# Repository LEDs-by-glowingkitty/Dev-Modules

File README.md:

# Dev-Modules
A collection of development modules for electrical engineers, who work on new PCB designs.

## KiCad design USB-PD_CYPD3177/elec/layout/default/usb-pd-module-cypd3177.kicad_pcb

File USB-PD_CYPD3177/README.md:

# Dev-Module / USB-PD Module / CYPD3177
A PCB module for hardware developers who want to easily test and build prototypes that include the CYPD3177 USB-PD IC.

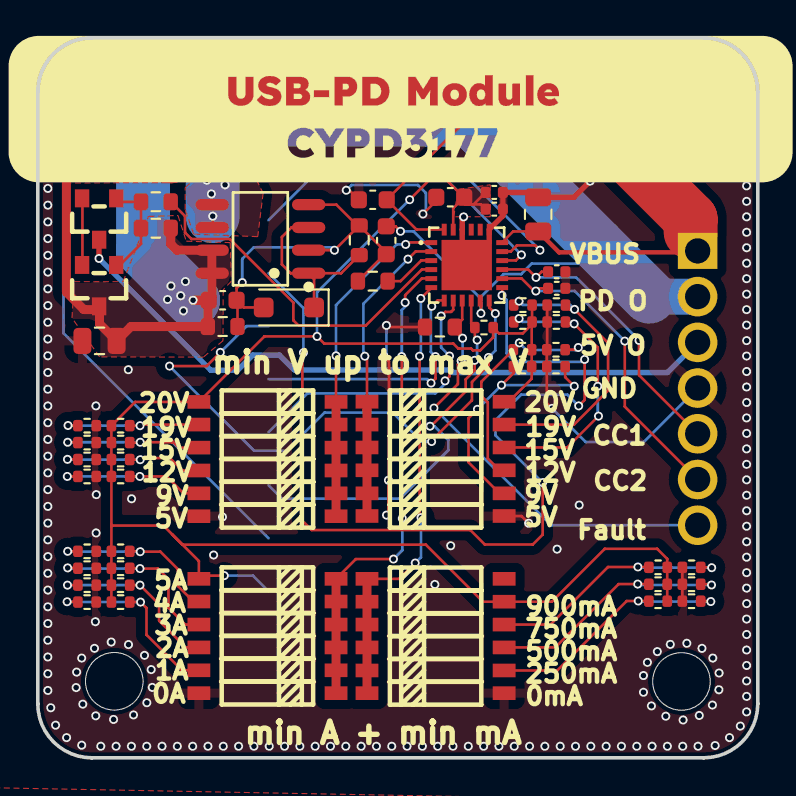
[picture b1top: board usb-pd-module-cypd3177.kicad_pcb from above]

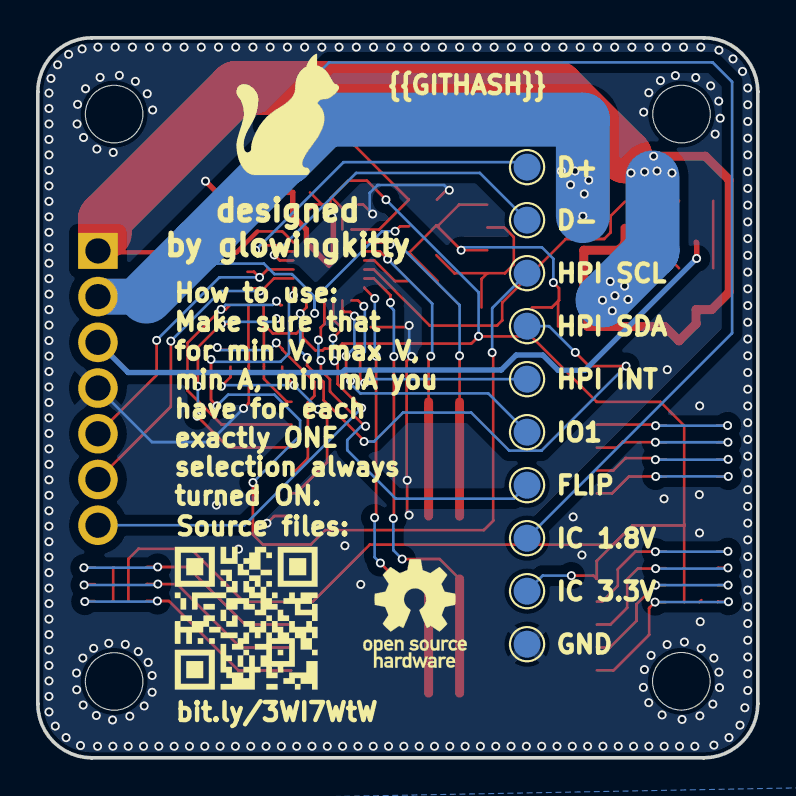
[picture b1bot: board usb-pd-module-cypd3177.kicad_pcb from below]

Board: 2 copper layers, 40.0 x 40.0 mm, 71 parts (10 on the bottom side), 41 nets.

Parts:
C1, C6: 16V 3.3uF X7R ±10% 0805 Multilayer Ceramic Capaci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; C0805
C2, C3, C7, C8: 50V 1uF X5R ±10% 0603 Multilayer Ceramic Capacito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; C0603
C4, C5: 50V 390pF NP0 ±5% 0402 Multilayer Ceramic Capacit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; C0402
C9, C10: 16V 100nF X7R ±10% 0402 Multilayer Ceramic Capaci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; C0402
DZ1: D_SOD-123F
Q1: SOP-8_L4.9-W3.9-P1.27-LS6.0-BL
Q2, Q3: SOT-23_L2.9-W1.3-P1.90-LS2.4-BR
R1: 100mW Thick Film Resistors 75V ±100ppm/℃ ±1% 10kΩ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; R0603
R2, R5: 100mW Thick Film Resistors 75V ±100ppm/℃ ±1% 1kΩ 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; R0603
R3, R4: 100mW Thick Film Resistors 75V ±100ppm/℃ ±1% 49.9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; R0603
R6: 100mW Thick Film Resistors 75V ±100ppm/℃ ±1% 100k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; R0603
R7: 62.5mW Thick Film Resistors 50V ±100ppm/℃ ±1% 2kΩ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; R0402
R8, R10, R12, R13, R14, R16, R18, R20, R21, R22, R24, R26, R28, R29, R30, R32, R34, R36, R37: 62.5mW Thick Film Resistors 50V ±100ppm/℃ ±1% 5.1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; R0402
R9, R17, R25, R33: 62.5mW Thick Film Resistors 50V ±100ppm/℃ ±1% 1kΩ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; R0402
R11, R19, R27, R35: 62.5mW Thick Film Resistors 50V ±100ppm/℃ ±1% 2.4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; R0402
R15, R23, R31: 62.5mW Thick Film Resistors 50V ±100ppm/℃ ±1% 10k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; R0402
U1, U2, U3, U4: SW-SMD_12P-L9.2-W5.4-P1.27-LS8.5
U5: CONN-TH_XY308-2.54-7P
U6, U7, U8, U9, U10, U11, U12, U13, U14, U15: TestPoint_Pad_D1.5mm
U16, U17, U18, U19: MountingHole_3.2mm_M3
U20: TQFN-24_L4.0-W4.0-P0.50-TL-EP2.8

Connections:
cc1: C4.1, U5.5, U20.15
cc2: C5.1, U5.6, U20.14
dminus: U8.1, U20.16
dplus: U7.1, U20.17
fault: R6.1, U5.7, U20.9
flip: R7.1, U15.1, U20.10
gate: Q2.1, Q3.1, R4.2, R5.1
gnd: C1.2, C4.2, C5.2, C6.2, C7.2, C8.2, C9.2, C10.2, R6.2, R9.2, R11.2, R13.2, R15.2, R17.2, R19.2, R21.2, R23.2, R25.2, R27.2, R29.2, R31.2, R33.2, R35.2, R37.2, U1.12, U2.7, U3.12, U4.7, U5.4, U6.1, U20.19, U20.22, U20.25
gpio_1: U14.1, U20.8
hpi_int: U13.1, U20.7
hpi_scl: U12.1, U20.13
hpi_sda: U11.1, U20.12
isnk_coarse: U3.1, U3.2, U3.3, U3.4, U3.5, U3.6, U20.5
isnk_fine: U4.1, U4.2, U4.3, U4.4, U4.5, U4.6, U20.6
power_out_5v_load_switch.p_mosfet_1-source: Q2.2, Q3.2
power_out_vbus_load_switch.dual_p_mosfet-gnd: C2.2, C3.2, DZ1.2, Q1.2, Q1.4, R1.2, R2.2, R3.2
power_out_vbus_load_switch.dual_p_mosfet-source: DZ1.1, Q1.1, Q1.3, R3.1
safe_pwr_en: R5.2, U20.4
vbus_fet_en: R2.1, U20.3
vbus_in: C1.1, C2.1, C6.1, Q1.7, Q1.8, Q2.3, R1.1, R4.1, U5.1, U20.18
vbus_max: U2.1, U2.2, U2.3, U2.4, U2.5, U2.6, U20.2
vbus_min: U1.1, U1.2, U1.3, U1.4, U1.5, U1.6, U20.1
vcc: Q3.3, U5.3
vccd: C7.1, U10.1, U20.24
vdc_out: C3.1, Q1.5, Q1.6, U5.2, U20.11
vddd: C8.1, C9.1, C10.1, R7.2, R8.1, R10.1, R12.1, R14.1, R16.1, R18.1, R20.1, R22.1, R24.1, R26.1, R28.1, R30.1, R32.1, R34.1, R36.1, U1.7, U2.12, U3.7, U4.11, U9.1, U20.23
voltage_dividers_and_dip_switches.coarse_current_min_1a_voltage_divider-out: R24.2, R25.1, U3.11
voltage_dividers_and_dip_switches.coarse_current_min_2a_voltage_divider-out: R26.2, R27.1, U3.10
voltage_dividers_and_dip_switches.coarse_current_min_3a_voltage_divider-out: R28.2, R29.1, U3.9
voltage_dividers_and_dip_switches.coarse_current_min_4a_voltage_divider-out: R30.2, R31.1, U3.8
voltage_dividers_and_dip_switches.fine_current_min_250ma_voltage_divider-out: R32.2, R33.1, U4.8
voltage_dividers_and_dip_switches.fine_current_min_500ma_voltage_divider-out: R34.2, R35.1, U4.9
voltage_dividers_and_dip_switches.fine_current_min_750ma_voltage_divider-out: R36.2, R37.1, U4.10
voltage_dividers_and_dip_switches.maximum_voltage_9v_voltage_divider-out: R16.2, R17.1, U2.8
voltage_dividers_and_dip_switches.maximum_voltage_12v_voltage_divider-out: R18.2, R19.1, U2.9
voltage_dividers_and_dip_switches.maximum_voltage_15v_voltage_divider-out: R20.2, R21.1, U2.10
voltage_dividers_and_dip_switches.maximum_voltage_19v_voltage_divider-out: R22.2, R23.1, U2.11
voltage_dividers_and_dip_switches.minimum_voltage_9v_voltage_divider-out: R8.2, R9.1, U1.11
voltage_dividers_and_dip_switches.minimum_voltage_12v_voltage_divider-out: R10.2, R11.1, U1.10
voltage_dividers_and_dip_switches.minimum_voltage_15v_voltage_divider-out: R12.2, R13.1, U1.9
voltage_dividers_and_dip_switches.minimum_voltage_19v_voltage_divider-out: R14.2, R15.1, U1.8

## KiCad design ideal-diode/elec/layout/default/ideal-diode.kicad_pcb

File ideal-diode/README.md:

# ideal-diode

Wooohooo a new package!

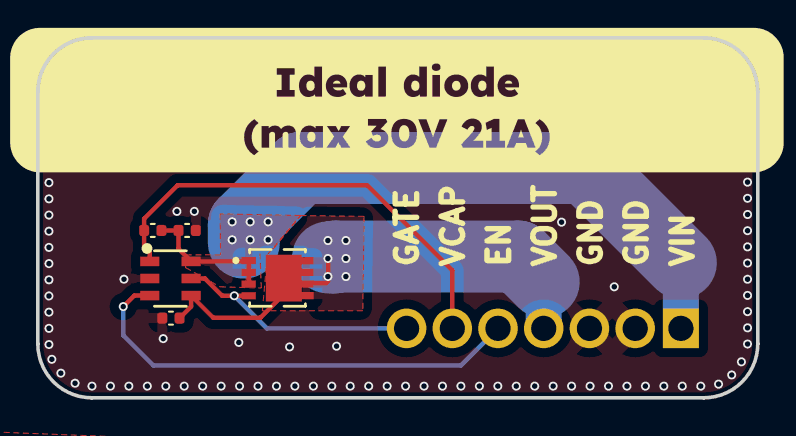
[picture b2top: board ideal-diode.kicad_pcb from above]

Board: 2 copper layers, 40.0 x 20.0 mm, 8 parts (0 on the bottom side), 6 nets.

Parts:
C1: 50V 22nF X7R ±10% 0402 Multilayer Ceramic Capacit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; C0402
C2, C3: 16V 100nF X7R ±10% 0402 Multilayer Ceramic Capaci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; C0402
Q1: PDFN-8_L3.2-W3.0-P0.65-LS3.3-BL-1
U1: SOT-23-6_L2.9-W1.6-P0.95-LS2.8-BL
U2: CONN-TH_XY308-2.54-7P
U3, U4: MountingHole_3.2mm_M3

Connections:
anode: C1.1, C2.1, Q1.1, Q1.2, Q1.3, U1.6, U2.1
cathode: C3.1, Q1.5, Q1.6, Q1.7, Q1.8, Q1.9, U1.4, U2.4
en: U1.3, U2.5
gate: Q1.4, U1.5, U2.7
gnd: C1.2, C3.2, U1.2, U2.2, U2.3
vcap: C2.2, U1.1, U2.6

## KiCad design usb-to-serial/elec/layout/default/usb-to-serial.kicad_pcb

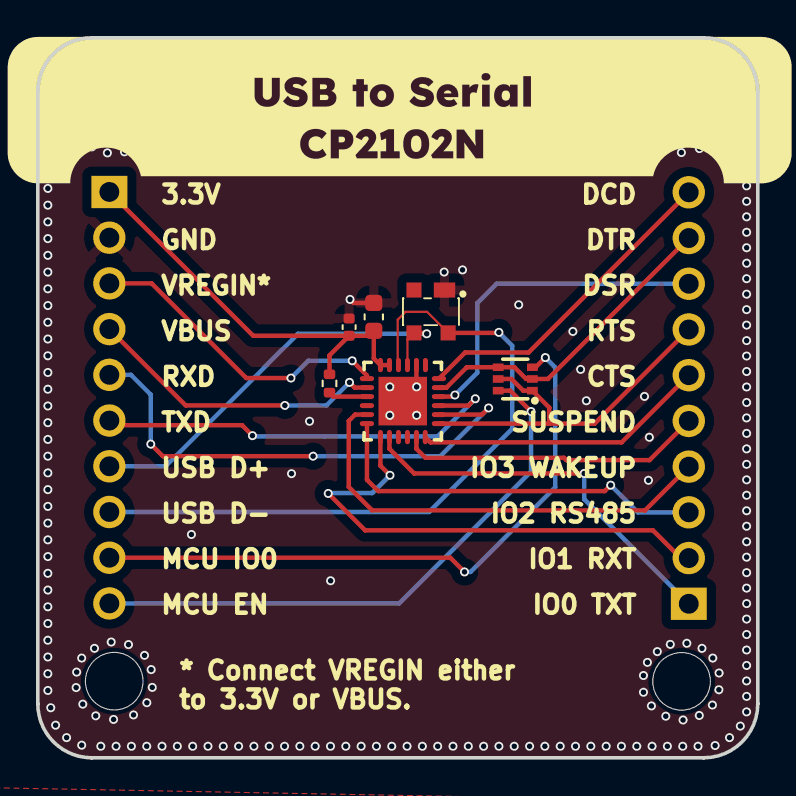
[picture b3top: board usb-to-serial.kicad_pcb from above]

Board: 2 copper layers, 40.0 x 40.0 mm, 12 parts (0 on the bottom side), 21 nets.

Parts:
C1: 16V 100nF X7R ±10% 0402 Multilayer Ceramic Capaci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; C0402
C2: 10V 10uF X5R ±10% 0603 Multilayer Ceramic Capacit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; C0603
R1: 62.5mW Thick Film Resistors 50V ±100ppm/℃ ±1% 1kΩ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; R0402
U1: SOT-143-4_L2.9-W1.3-P1.92-LS2.4-BL
U2: SC-70-6_L2.2-W1.3-P0.65-LS2.1-BR
U3: QFN-24_L4.0-W4.0-P0.50-TL-EP2.6
U4, U5: CONN-TH_10P-P2.54_MX128-2.54-10P-GN01-CU-Y-A
U6, U7, U8, U9: MountingHole_3.2mm_M3

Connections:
cts: U3.18, U5.6
dcd: U3.24, U5.10
dminus: U1.4, U3.4, U4.8
dplus: U1.3, U3.3, U4.7
dsr: U3.22, U5.8
dtr: U2.2, U2.4, U3.23, U5.9
gnd: C1.2, C2.2, U1.1, U3.2, U3.25, U4.2
gpio_0_txt: U3.14, U5.1
gpio_1_rxt: U3.13, U5.2
gpio_2_rs485: U3.12, U5.3
gpio_3_wakeup: U3.11, U5.4
mcu_en: U2.6, U4.10
mcu_io0: U2.3, U4.9
rstb: R1.1, U3.9
rts: U2.1, U2.5, U3.19, U5.7
rxd: U3.20, U4.5
suspend: U3.17, U5.5
txd: U3.21, U4.6
vbus: U3.8, U4.4
vio: C1.1, C2.1, R1.2, U3.5, U3.6, U4.1
vregin: U3.7, U4.3

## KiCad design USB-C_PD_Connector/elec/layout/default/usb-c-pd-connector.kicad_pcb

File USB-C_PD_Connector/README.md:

# Dev-Module / USB-C PD Connector
A PCB module for hardware developers who want to easily test and build prototypes that include a USB PD capable USB-C port (that can handle up to 100W at 20V 5A).

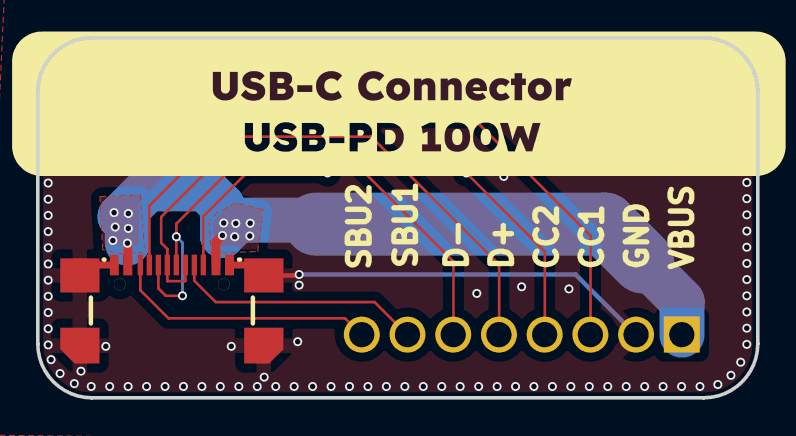
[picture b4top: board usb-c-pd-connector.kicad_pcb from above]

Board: 2 copper layers, 40.0 x 20.0 mm, 4 parts (0 on the bottom side), 8 nets.

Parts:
U1: USB-C-SMD_TYPE-C-31-M-22
U2: CONN-TH_XY308-2.54-8P
U3, U4: MountingHole_3.2mm_M3

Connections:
cc1: U1.4, U2.3
cc2: U1.10, U2.4
dm: U1.5, U1.7, U2.6
dp: U1.6, U1.8, U2.5
gnd: U1.1, U1.12, U1.13, U1.14, U1.15, U1.16, U2.2
sbu1: U1.9, U2.7
sbu2: U1.3, U2.8
vbus: U1.2, U1.11, U2.1

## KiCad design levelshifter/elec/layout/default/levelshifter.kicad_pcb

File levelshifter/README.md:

# levelshifter

Wooohooo a new package!

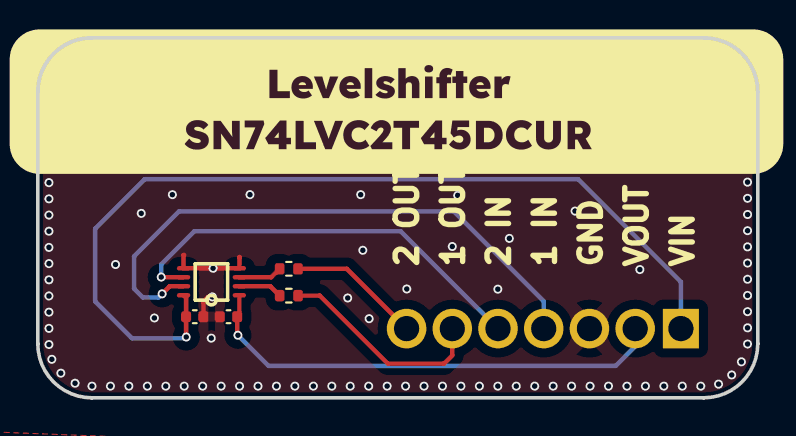
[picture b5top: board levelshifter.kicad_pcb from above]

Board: 2 copper layers, 40.0 x 20.0 mm, 8 parts (0 on the bottom side), 9 nets.

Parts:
C1, C2: 16V 100nF X7R ±10% 0402 Multilayer Ceramic Capaci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; C0402
R1, R2: 62.5mW Thick Film Resistors ±100ppm/℃ ±1% 62Ω 040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; R0402
U1: VSSOP-8_L2.4-W2.1-P0.50-LS3.2-BR
U2: CONN-TH_XY308-2.54-7P
U3, U4: MountingHole_3.2mm_M3

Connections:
a1: R1.2, U1.2
a2: R2.2, U1.3
b1: U1.7, U2.4
b2: U1.6, U2.5
data_in_1_resistor-vcc: R1.1, U2.6
data_in_2_resistor-vcc: R2.1, U2.7
gnd: C1.2, C2.2, U1.4, U1.5, U2.3
vcc: C1.1, U1.8, U2.1
vcc-1: C2.1, U1.1, U2.2

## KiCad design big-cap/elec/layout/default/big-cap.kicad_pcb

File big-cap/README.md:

# big-cap

Wooohooo a new package!

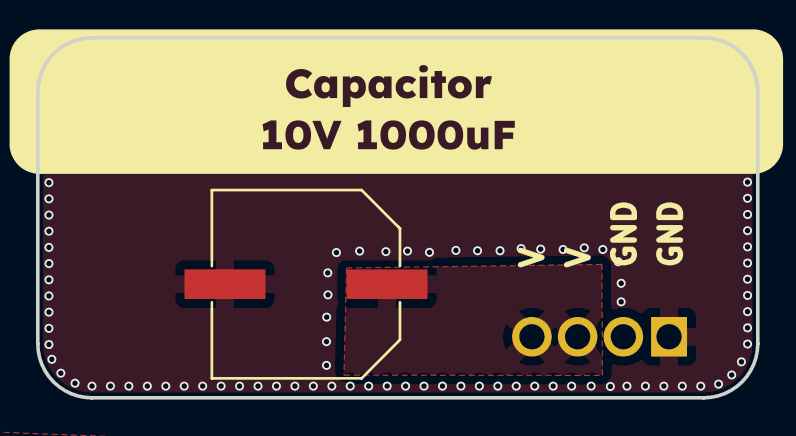
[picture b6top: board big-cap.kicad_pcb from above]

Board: 2 copper layers, 40.0 x 20.0 mm, 4 parts (0 on the bottom side), 2 nets, no tracks yet.

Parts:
C1: 1000uF +/- 20%; CAP-SMD_BD10.0-L10.3-W10.3-LS10.9-FD
U1: CONN-TH_XY308-2.54-4P
U2, U3: MountingHole_3.2mm_M3

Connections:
_1: C1.1, U1.1, U1.2
_3: C1.2, U1.3, U1.4

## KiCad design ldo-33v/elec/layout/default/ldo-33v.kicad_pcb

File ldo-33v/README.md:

# ldo-33v

Wooohooo a new package!

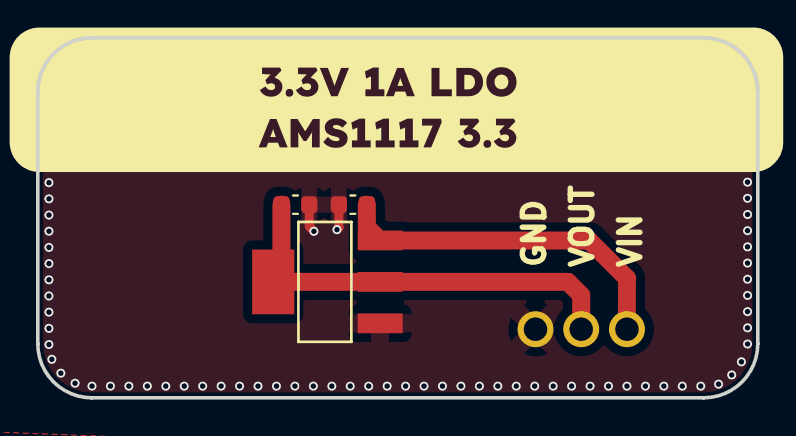
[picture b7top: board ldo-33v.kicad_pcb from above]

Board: 2 copper layers, 40.0 x 20.0 mm, 6 parts (0 on the bottom side), 3 nets.

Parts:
C1, C2: 10V 10uF X5R ±10% 0603 Multilayer Ceramic Capacit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; C0603
U1: SOT-223-3_L6.5-W3.4-P2.30-LS7.0-BR
U2: CONN-TH_XY308-2.54-3P
U3, U4: MountingHole_3.2mm_M3

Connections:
gnd: C1.2, C2.2, U1.1, U2.3
vcc: C1.1, U1.3, U2.1
vout: C2.1, U1.2, U1.4, U2.2

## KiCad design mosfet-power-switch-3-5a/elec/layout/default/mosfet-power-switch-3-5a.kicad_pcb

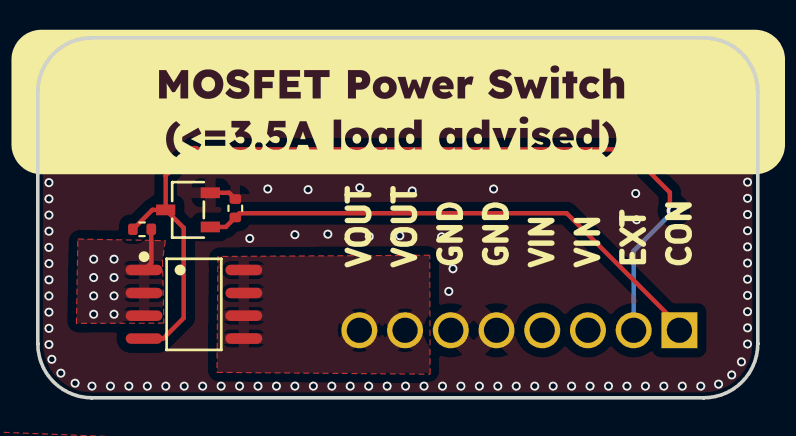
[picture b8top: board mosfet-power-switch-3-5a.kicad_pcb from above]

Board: 2 copper layers, 40.0 x 20.0 mm, 7 parts (0 on the bottom side), 5 nets.

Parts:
Q1: SOIC-8_L4.9-W3.9-P1.27-LS6.0-BL
Q2: SOT-23-3_L2.9-W1.6-P1.90-LS2.8-BR
R1, R2: 62.5mW Thick Film Resistors 50V ±100ppm/℃ ±1% 100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; R0402
U1: CONN-TH_XY308-2.54-8P
U2, U3: MountingHole_3.2mm_M3

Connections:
_2: Q1.4, Q2.3, R1.1, U1.2
control: Q2.1, R2.1, U1.1
gnd: Q2.2, R2.2, U1.5, U1.6
mosfet_power_switch-vcc: Q1.1, Q1.2, Q1.3, R1.2, U1.3, U1.4
mosfet_power_switch-vcc-1: Q1.5, Q1.6, Q1.7, Q1.8, U1.7, U1.8

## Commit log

2024-04-28 added usb pd module
2024-05-11 clean up code, remove empty spaces
2024-05-11 fixed 3d model positions and links
2024-05-14 finished dev module for USB PD pcb layout
2024-05-14 added usb c pd connector dev module (in dev)
2024-05-15 completed pcb module for USB-C connector for 100W USB PD
2024-05-15 fix design rule issues
2024-05-28 added assertions for better testing components
2024-06-05 added pcb for big cap
2024-06-05 added 'designed by glowingkitty' silkscreen
2024-06-05 added designed by glowingkitty
2024-06-05 updated documents
2024-06-05 added 3.3v ldo module
2024-06-06 fixed ldo schematic code
2024-06-06 added levelshifter board
2024-06-06 removed not used file
2024-06-10 added esp32 module
2024-06-10 added screw terminals for esp32 pcb
2024-06-10 renamed variables
2024-06-11 updated footprints and pcb layout
2024-06-11 added base for new mosfet power switch dev board
2024-06-13 added mosfets and connections
2024-06-13 added screw terminal and connections for mosfet power switch
2024-06-13 placed components on board
2024-06-13 added module for microphone (base files)
2024-06-13 added all connections for mic dev module
2024-06-14 replaced microphone model with one that is available and from well known company
2024-06-14 completed mic dev board layouting
2024-06-14 removed silkscreen for pinheader
2024-06-14 removed silkscreen
2024-06-14 adapted pin header position and removed silkscreen
2024-06-14 remove silkscreen
2024-06-14 added usb to serial base
2024-06-15 added usb to serial with assertions
2024-06-18 made further changes to usb to serial
2024-06-18 updated pin descriptions and added screw terminals
2024-06-18 fixed autoreset
2024-06-19 updated usb to serial dev module, connected traces
2024-06-23 finished usb to serial layout
2024-06-23 fixed comments
2024-06-24 added base files for ideal-diode
2024-06-24 completed schematic for ideal diode
2024-06-24 added pcb layout for ideal-diode
2024-06-27 updated mosfets for USB PD IC
2024-06-27 rearranged usb pd ic code and added assertions
2024-06-28 fixed assertion error
2024-06-29 updated layout
2024-06-29 switched to caps capable of 50V, to handle USB PD voltage of up to 20V
2024-06-29 added missing footprint
2024-08-28 added todos
2024-08-28 updated todos
2024-08-28 added comments
